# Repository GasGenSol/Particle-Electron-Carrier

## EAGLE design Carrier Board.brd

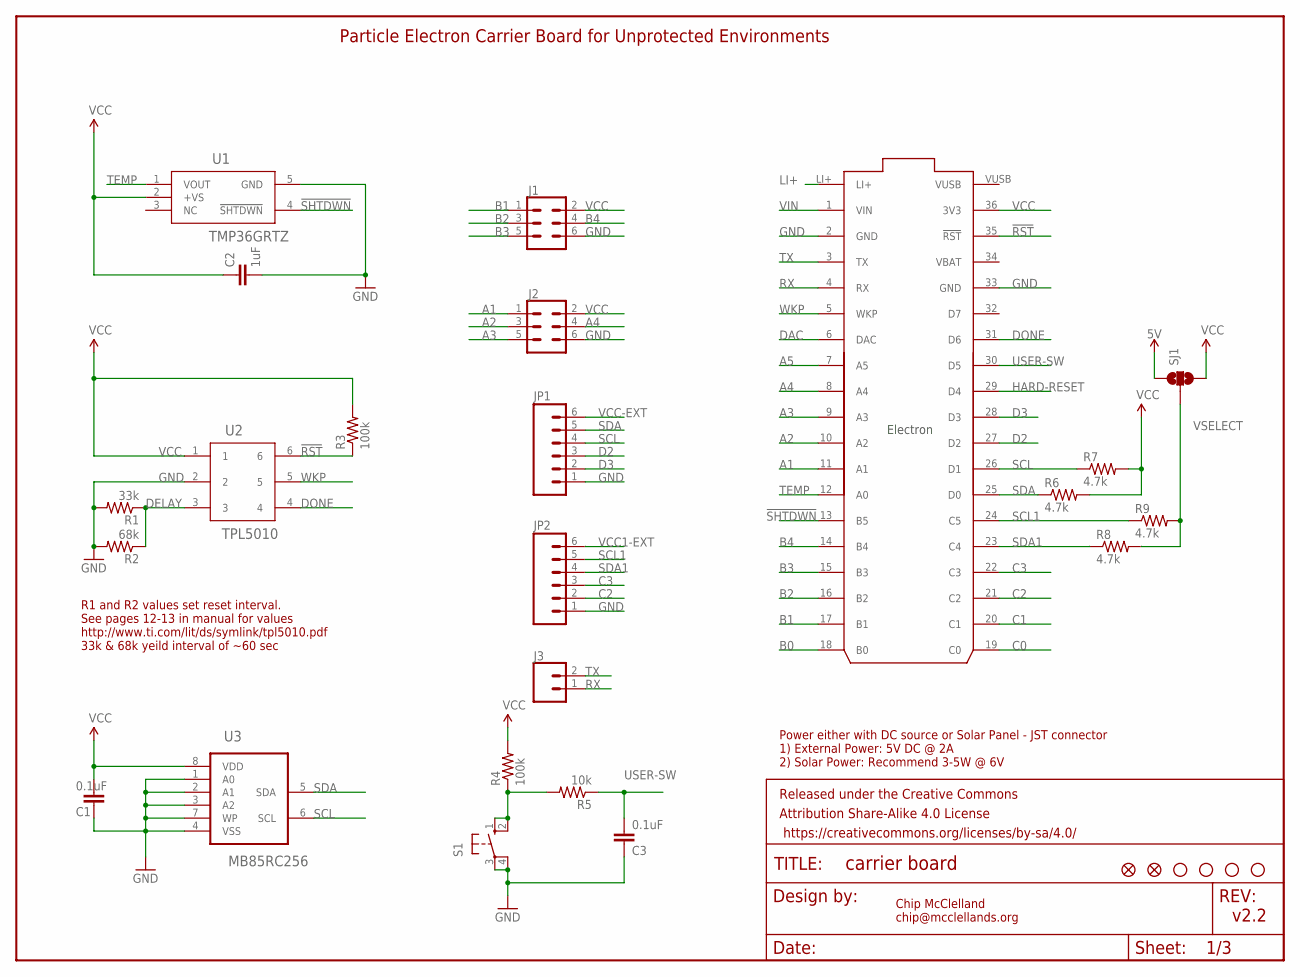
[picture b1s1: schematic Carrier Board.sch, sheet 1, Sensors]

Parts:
C1, C3: 0.1uF; 0805
C2: 1uF; 0805
FD1, FD2: FIDUCIALUFIDUCIAL; FIDUCIAL-MICRO
FRAME1: FRAME-LETTER; CREATIVE_COMMONS
J1, J2: CONN_03X22X3_SILK_MALE_PTH; 2X3
J3: CONN_02; 1X02
JP1, JP2: M06LOCK; 1X06_LOCK
JP3, JP4, JP5, JP6: STAND-OFF
R1: 33k; 0805
R2: 68k; 0805
R3, R4: 100k; 0805
R5: 10k; 0805
R6, R7, R8, R9: 4.7k; 0805
S1: 10-XX; B3F-10XX
SJ1: SOLDERJUMPER_2WAYPASTE1&2; SJ_3_PASTE1&2
U1: TMP36GRTZ; RJ_5
U2: TPL5010; TSOT-23
U3: MB85RC256; SOIC127P600X175-8N
U4: Particle Electron; ELECTON-PWR-PINS

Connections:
5V: SJ1.1; also elsewhere on the board
!RST: R3.1, U2.6, U4.35 (!RST)
!SHTDWN: U1.4 (!SHTDWN), U4.13 (B5)
A1: J2.1, U4.11 (A1)
A2: J2.3, U4.10 (A2)
A3: J2.5, U4.9 (A3)
A4: J2.4, U4.8 (A4)
A5: U4.7 (A5)
B0: U4.18 (B0)
B1: J1.1, U4.17 (B1)
B2: J1.3, U4.16 (B2)
B3: J1.5, U4.15 (B3)
B4: J1.4, U4.14 (B4)
C0: U4.19 (C0)
C1: U4.20 (C1)
C2: JP2.2, U4.21 (C2); also elsewhere on the board
C3: JP2.3, U4.22 (C3); also elsewhere on the board
D2: JP1.3, U4.27 (D2); also elsewhere on the board
D3: JP1.2, U4.28 (D3); also elsewhere on the board
DAC: U4.6 (DAC)
DELAY: R1.1, R2.1, U2.3
DONE: U2.4, U4.31 (D6)
GND: C1.2, C2.2, C3.2, J1.6, J2.6, JP1.1, JP2.1, R1.2, R2.2, S1.3, S1.4 (P1), U1.5 (GND), U2.2, U3.1 (A0), U3.2 (A1), U3.3 (A2), U3.4 (VSS), U3.7 (WP), U4.2 (GND), U4.33 (GND); also elsewhere on the board
HARD-RESET: U4.29 (D4); also elsewhere on the board
LI+: U4.LI+; also elsewhere on the board
unnamed: R4.1, R5.2, S1.1 (S), S1.2 (S1)
RX: J3.1, U4.4 (RX)
SCL: JP1.4, R7.1, U3.6 (SCL), U4.26 (D1); also elsewhere on the board
SCL1: JP2.5, R9.1, U4.24 (C5); also elsewhere on the board
SDA: JP1.5, R6.1, U3.5 (SDA), U4.25 (D0); also elsewhere on the board
SDA1: JP2.4, R8.1, U4.23 (C4); also elsewhere on the board
TEMP: U1.1 (VOUT), U4.12 (A0)
TX: J3.2, U4.3 (TX)
USER-SW: C3.1, R5.1, U4.30 (D5)
VBAT: U4.34 (VBAT)
VCC: C1.1, C2.1, J1.2, J2.2, R3.2, R4.2, R6.2, R7.2, SJ1.3, U1.2 (+VS), U2.1, U3.8 (VDD), U4.36 (3V3); also elsewhere on the board
VCC1-EXT: JP2.6; also elsewhere on the board
VCC-EXT: JP1.6; also elsewhere on the board
VIN: U4.1 (VIN); also elsewhere on the board
VSELECT: R8.2, R9.2, SJ1.2; also elsewhere on the board
WKP: U2.5, U4.5 (WKP)

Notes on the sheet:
Chip McClelland chip@mcclellands.org
v2.2
Power either with DC source or Solar Panel - JST connector 1) External Power: 5V DC @ 2A 2) Solar Power: Recommend 3-5W @ 6V
Particle Electron Carrier Board for Unprotected Environments
R1 and R2 values set reset interval. See pages 12-13 in manual for values http://www.ti.com/lit/ds/symlink/tpl5010.pdf 33k & 68k yeild interval of ~60 sec

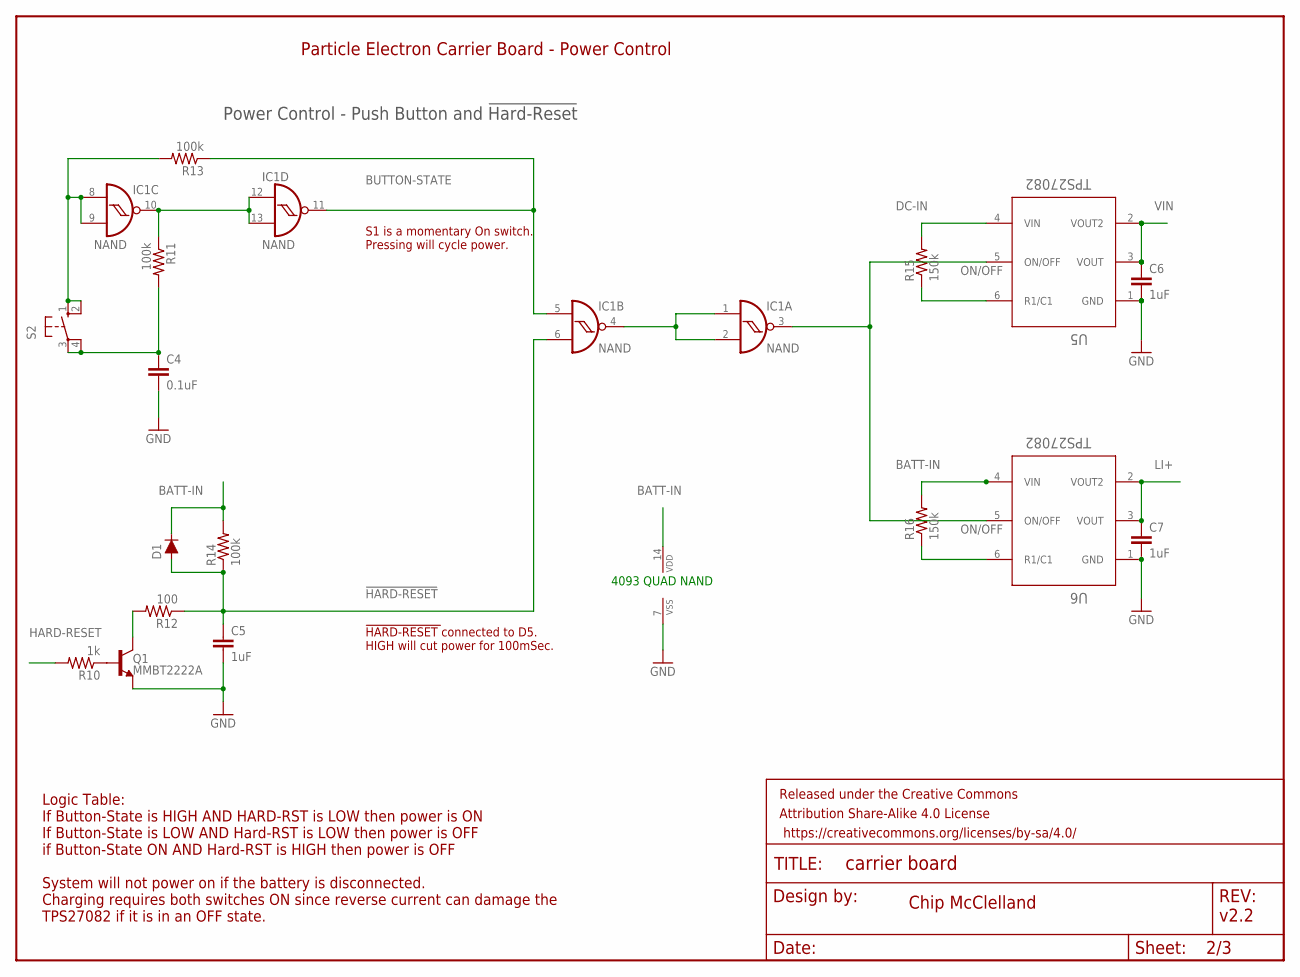
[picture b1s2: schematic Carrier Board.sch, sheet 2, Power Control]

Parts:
C4: 0.1uF; 0805
C5, C6, C7: 1uF; 0805
D1: DIODE-BAS16J; SOD-323
FRAME2: FRAME-LETTER; CREATIVE_COMMONS
IC1: NAND; MC14093B-TSSOP14
Q1: MMBT2222A; SOT23-3
R10: 1k; 0805
R11, R13, R14: 100k; 0805
R12: 100; 0805
R15, R16: 150k; 0805
S2: 40-XX-ROUND; B3F-40XX-ROUND
U5, U6: TPS27082; TSOT-23

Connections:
!HARD-RESET: C5.1, D1.A, IC1.6 (I1), R12.1, R14.1
BATT-IN: D1.C, IC1.14 (VDD), R14.2, R16.2, U6.4 (VIN); also elsewhere on the board
BUTTON-STATE: IC1.5 (I0), IC1.11 (O), R13.1
DC-IN: R15.2, U5.4 (VIN); also elsewhere on the board
GND: C4.2, C5.2, C6.2, C7.2, IC1.7 (VSS), Q1.2 (E), U5.1 (GND), U6.1 (GND); also elsewhere on the board
HARD-RESET: R10.2; also elsewhere on the board
LI+: C7.1, U6.2 (VOUT2), U6.3 (VOUT); also elsewhere on the board
unnamed: IC1.1 (I0), IC1.2 (I1), IC1.4 (O)
unnamed: IC1.10 (O), IC1.12 (I0), IC1.13 (I1), R11.1
unnamed: R15.1, U5.6 (R1/C1)
unnamed: Q1.1 (B), R10.1
unnamed: R16.1, U6.6 (R1/C1)
unnamed: Q1.3 (C), R12.2
unnamed: C4.1, R11.2, S2.3, S2.4 (P1)
unnamed: IC1.8 (I0), IC1.9 (I1), R13.2, S2.1 (S), S2.2 (S1)
ON/OFF: IC1.3 (O), U5.5 (ON/OFF), U6.5 (ON/OFF)
VIN: C6.1, U5.2 (VOUT2), U5.3 (VOUT); also elsewhere on the board

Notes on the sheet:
Particle Electron Carrier Board - Power Control
4093 QUAD NAND
Power Control - Push Button and !Hard-Reset
Chip McClelland
v2.2
Logic Table: If Button-State is HIGH AND HARD-RST is LOW then power is ON If Button-State is LOW AND Hard-RST is LOW then power is OFF if Button-State ON AND Hard-RST is HIGH then power is OFF System will not power on if the battery is disconnected. Charging requires both switches ON since reverse 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
!HARD-RESET !connected to D5. HIGH will cut power for 100mSec.
S1 is a momentary On switch. Pressing will cycle power.

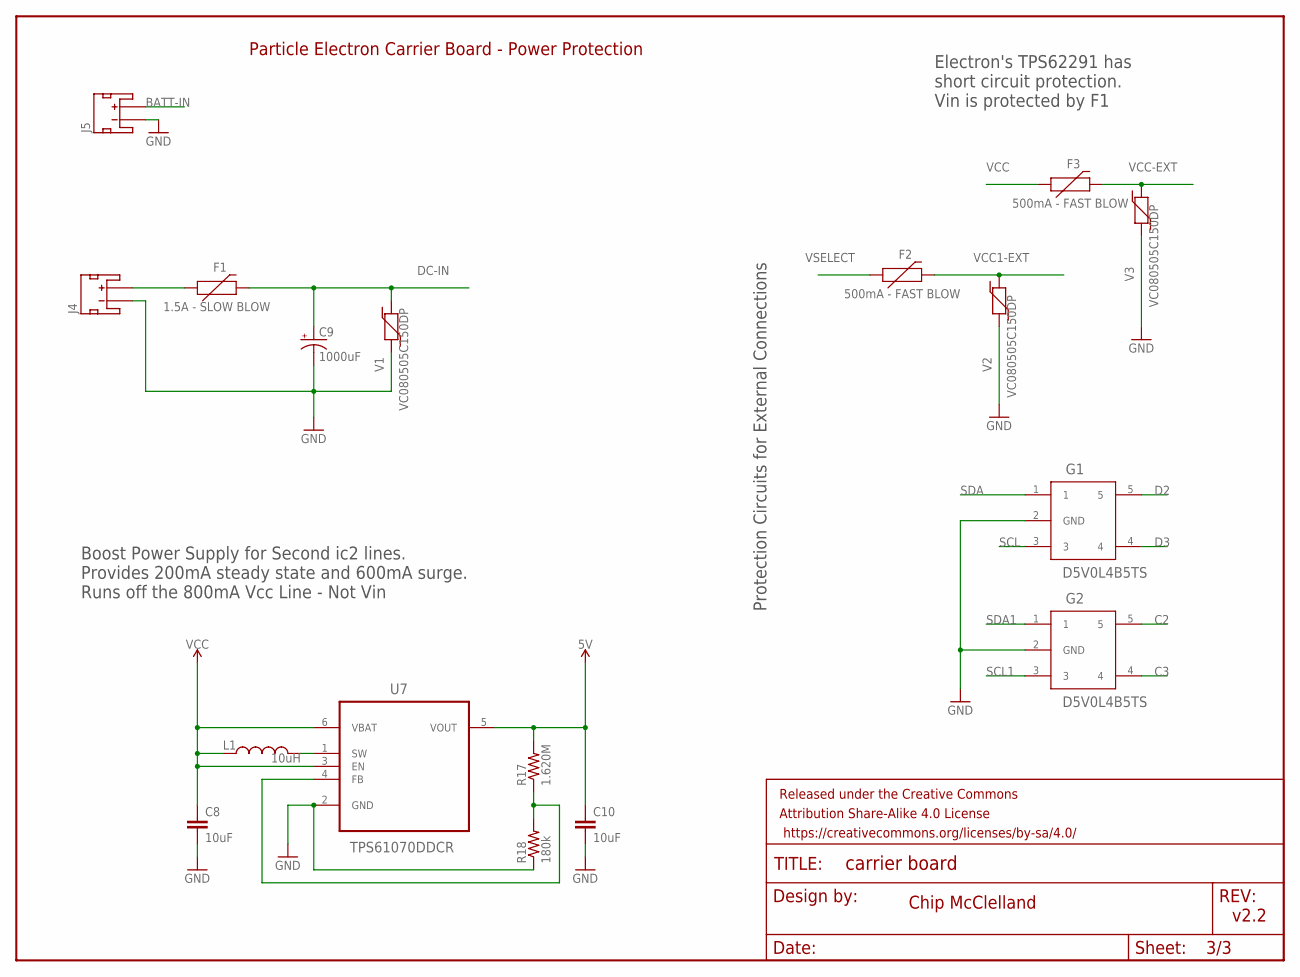
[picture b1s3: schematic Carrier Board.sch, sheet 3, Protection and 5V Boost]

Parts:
C8, C10: 10uF; 0805
C9: 1000uF; PANASONIC_G
F1: 1.5A - SLOW BLOW; 1206
F2, F3: 500mA - FAST BLOW; 1206
FRAME3: FRAME-LETTER; CREATIVE_COMMONS
G1, G2: D5V0L4B5TS; SOT-23-5
J4: 5V @ 2A; JST-2-SMD
J5: JST_2MM_MALE; JST-2-SMD
L1: 10uH; SDR0403
R17: 1.620M; 0805
R18: 180k; 0805
U7: TPS61070DDCR; SOT95P280X110-6N
V1, V2, V3: VC080505C150DP; 0805

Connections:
5V: C10.1, R17.2, U7.5 (VOUT); also elsewhere on the board
BATT-IN: J5.2 (+); also elsewhere on the board
C2: G2.5; also elsewhere on the board
C3: G2.4; also elsewhere on the board
D2: G1.5; also elsewhere on the board
D3: G1.4; also elsewhere on the board
DC-IN: C9.+, F1.2, V1.2; also elsewhere on the board
DC-IN-EXT: F1.1, J4.2 (+)
GND: C8.2, C9.-, C10.2, G1.2 (GND), G2.2 (GND), J4.1 (-), J5.1 (-), R18.1, U7.2 (GND), V1.1, V2.1, V3.1; also elsewhere on the board
unnamed: R17.1, R18.2, U7.4 (FB)
SCL: G1.3; also elsewhere on the board
SCL1: G2.3; also elsewhere on the board
SDA: G1.1; also elsewhere on the board
SDA1: G2.1; also elsewhere on the board
SW: L1.P$2 (2), U7.1 (SW)
VCC: C8.1, F3.1, L1.P$1 (1), U7.3 (EN), U7.6 (VBAT); also elsewhere on the board
VCC1-EXT: F2.2, V2.2; also elsewhere on the board
VCC-EXT: F3.2, V3.2; also elsewhere on the board
VSELECT: F2.1; also elsewhere on the board

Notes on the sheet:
Protection Circuits for External Connections
Electron's TPS62291 has short circuit protection. Vin is protected by F1
Boost Power Supply for Second ic2 lines. Provides 200mA steady state and 600mA surge. Runs off the 800mA Vcc Line - Not Vin
Chip McClelland
v2.2
Particle Electron Carrier Board - Power Protection

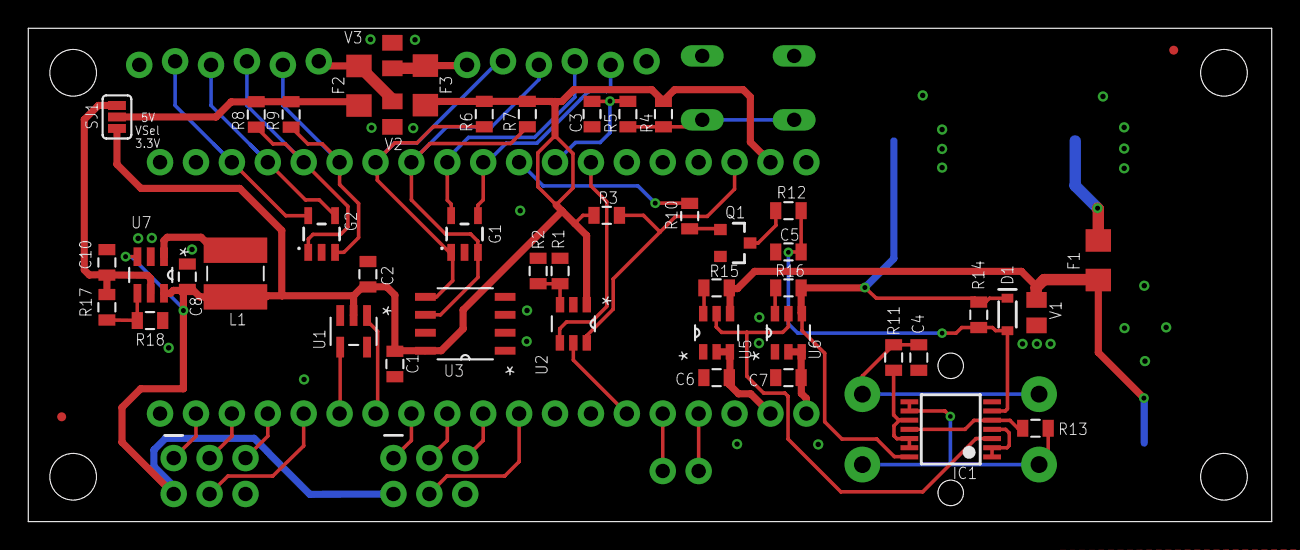
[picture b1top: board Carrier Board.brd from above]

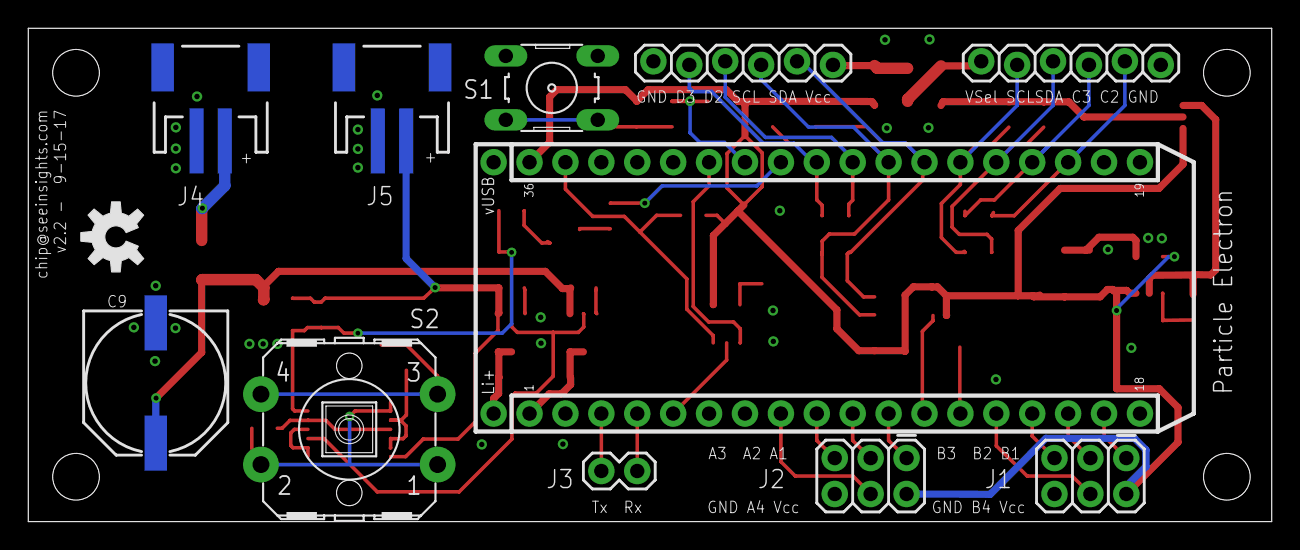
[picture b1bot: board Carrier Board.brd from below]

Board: 2 copper layers, 88.0 x 34.9 mm, 67 parts (12 on the bottom side), 51 nets.

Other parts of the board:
U$2: OSHW-LOGO-M

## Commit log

2017-09-15 Particle Electron Carrier v2.2
    This is the first version I feel good enough to release. Tested and
    refined over the past three months in the woods of North Carolina.
2017-09-18 Added BOM File
    Added Digikey BOM
2017-09-18 Added GitIgnore
2017-09-19 Deleted extra files.
2017-09-25 Adding gitignore
2018-06-30 Added Carrier Library

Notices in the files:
parts and their libraries:
SparkFun-Aesthetics: Licensing: Creative Commons ShareAlike 4.0 International - https://creativecommons.org/licenses/by-sa/4.0
SparkFun-Aesthetics: Released under the Creative Commons Attribution Share-Alike 4.0 License
SparkFun-Aesthetics: https://creativecommons.org/licenses/by-sa/4.0
